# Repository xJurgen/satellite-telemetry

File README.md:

# satellite-telemetry

This is a college project with an objective to create a CubeSat-like device from scratch.

The code is intended for a Blackpill (STM32F411CE) board and its functionality provides an access to the satellite sensors.
In the final design the Blackpill is connected to an RPi Zero W (V1.1) via USART1 and responds on the RPi requests.

Implemented features:
	
	- Command processing
	- Communication on USART1

Work in progress:
	
	- Light and temperature sensing using ADC

Planned features:

	- Battery management (solar panels input, battery output, shut-off when critically low level of battery..)
	- Gyroscope reading (?)

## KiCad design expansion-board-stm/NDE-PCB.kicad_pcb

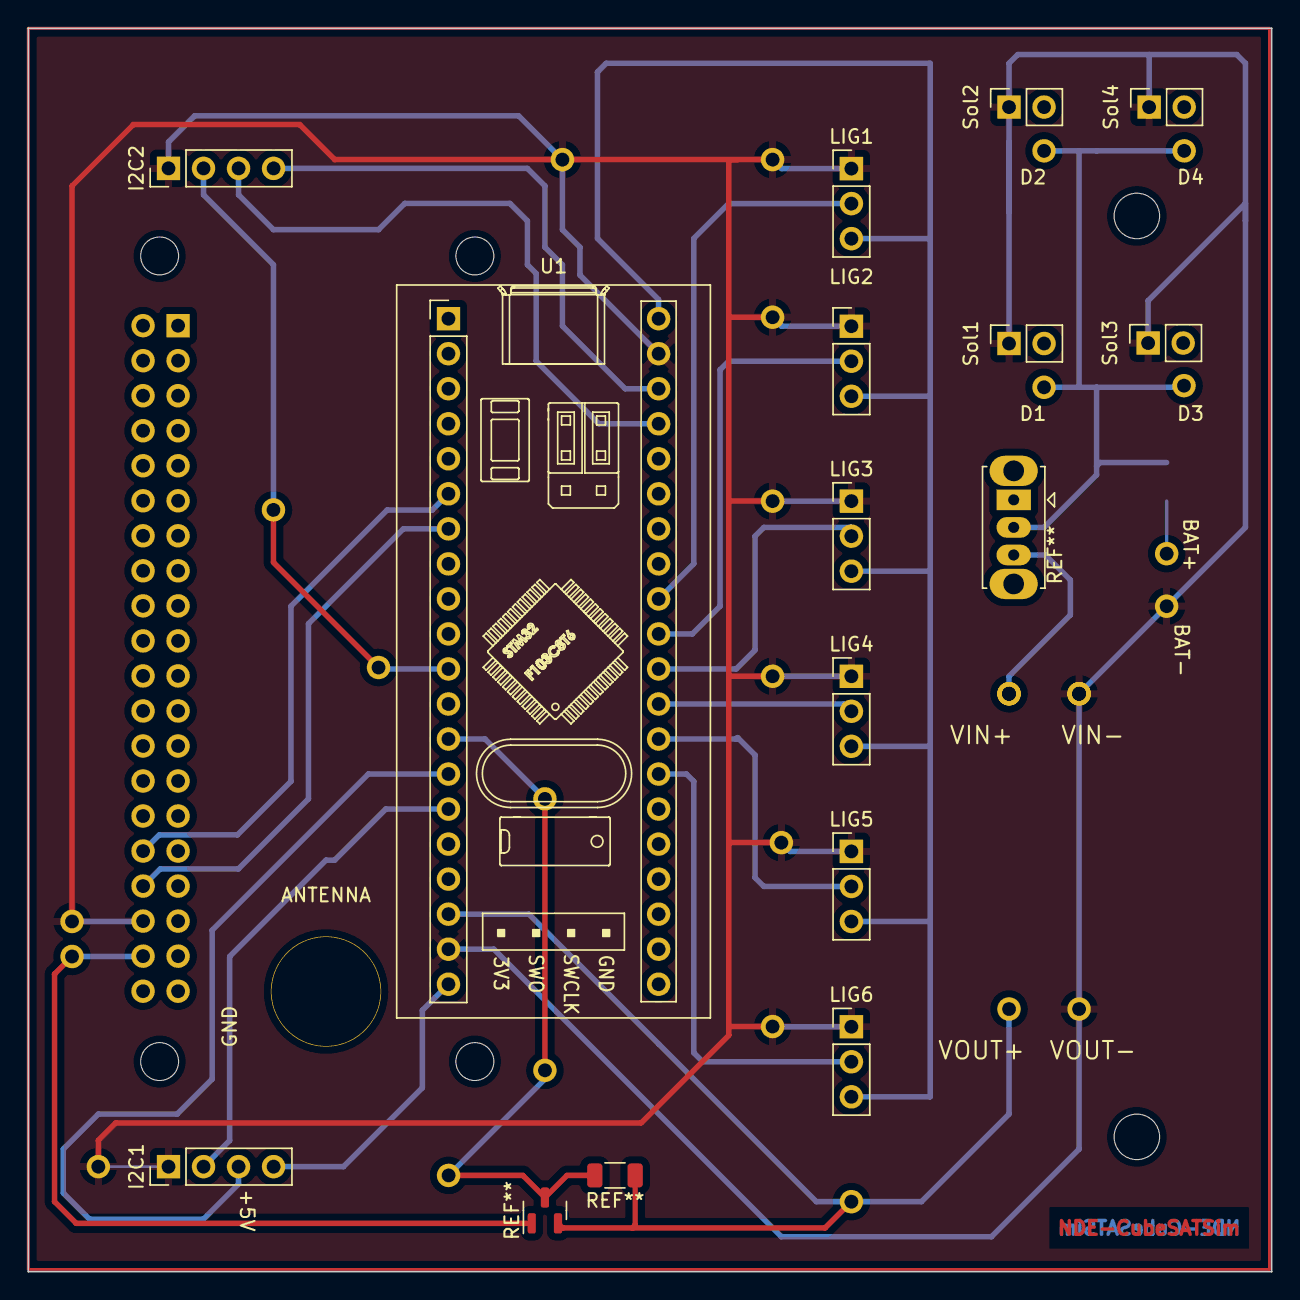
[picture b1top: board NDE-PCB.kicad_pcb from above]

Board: 2 copper layers, 90.2 x 90.2 mm, 15 parts (1 on the bottom side), 2 nets.

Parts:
ANTENNA: MountingHole_6mm_Pad_TopOnly
I2C1, I2C2: PinHeader_1x04_P2.54mm_Vertical
J1: Conn_02x20_Top_Bottom; PinHeader_2x20_P2.54mm_Vertical
LIG1, LIG2, LIG3, LIG4, LIG5, LIG6: PinHeader_1x03_P2.54mm_Vertical
Sol1, Sol2, Sol3, Sol4: PinSocket_1x02_P2.54mm_Vertical
U1: STM32F405RGTx; YAAJ_BluePill_1

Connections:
GND: I2C1.1, I2C2.1, J1.36, LIG1.1, LIG2.1, LIG3.1, LIG4.1, LIG5.1, LIG6.1, Sol1.1, Sol2.1, Sol3.1, Sol4.1, U1.gnd (PC8)
MCU: I2C1.2, I2C1.3, I2C1.4, I2C2.2, I2C2.3, I2C2.4, J1.32, J1.34, J1.38, LIG1.3, LIG1.adc6, LIG2.3, LIG2.adc5, LIG3.3, LIG3.adc4, LIG4.3, LIG4.adc3, LIG5.3, LIG5.adc2, LIG6.3, LIG6.adc1, U1.6 (PH1), U1.7 (NRST), U1.13 (VDDA), U1.18 (VSS), U1.20 (PA4), U1.27 (PB1), U1.28 (PB2), U1.29 (PB10), U1.30 (PB11), U1.31 (VCAP_1), U1.32 (VDD), U1.38 (PC7), U1.40 (PC9), U1.scl1 (PA0), U1.scl2 (PC6), U1.sda1 (PA1), U1.sda2 (PC3)

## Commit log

2023-02-27 Project setup
2023-02-27 Add command processing
2023-02-27 Add README info
2023-02-28 Add header file including all used standard libraries
2023-02-28 Prepare testing infrastructure for adc
2023-02-28 Tokenize and divide received data into chars and numbers
    Thanks to this the code can be more modular.
2023-02-28 Fix flags in Makefile so sprintf can work properly
2023-02-28 Check if called sensor number is in range
2023-02-28 Rename adc_light to adc_control since we will use it for a temperature as well
2023-02-28 Add automatic generation of header file containing the version and build time
    This file is already included in the main.c
2023-03-02 ADC reading.... [WIP]
2023-03-02 Add KiCAD files for the expansion board
    This commit doesn't contain the imported models used.
    I will add them in the future.
2023-03-20 UART: Fix communication, add new commands
    - Fix: HSE set to 96MHz to fix the UART communication
    - Addition: Parsing of the command "?" which returns all the data needed for the satellite antenna
2023-03-20 BMS: Prepare the .c and .h files for future work
2023-03-20 Fix ADC reading
2023-04-03 main: add support for command "R" which resets the device
2023-05-28 Working state for demo application
2023-05-28 Update PCB layout for the satellite + PDF Documentation of the project
    Known issues: Redesign needed for wrong traces near the RPi connector
    and for the MOSFET wrong orientation.
    Also needs to rethink the powerline and change the position of the
    fuse (place it between the DC/DC converter output and the MOSFET
    instead on the DC/DC converter input).
